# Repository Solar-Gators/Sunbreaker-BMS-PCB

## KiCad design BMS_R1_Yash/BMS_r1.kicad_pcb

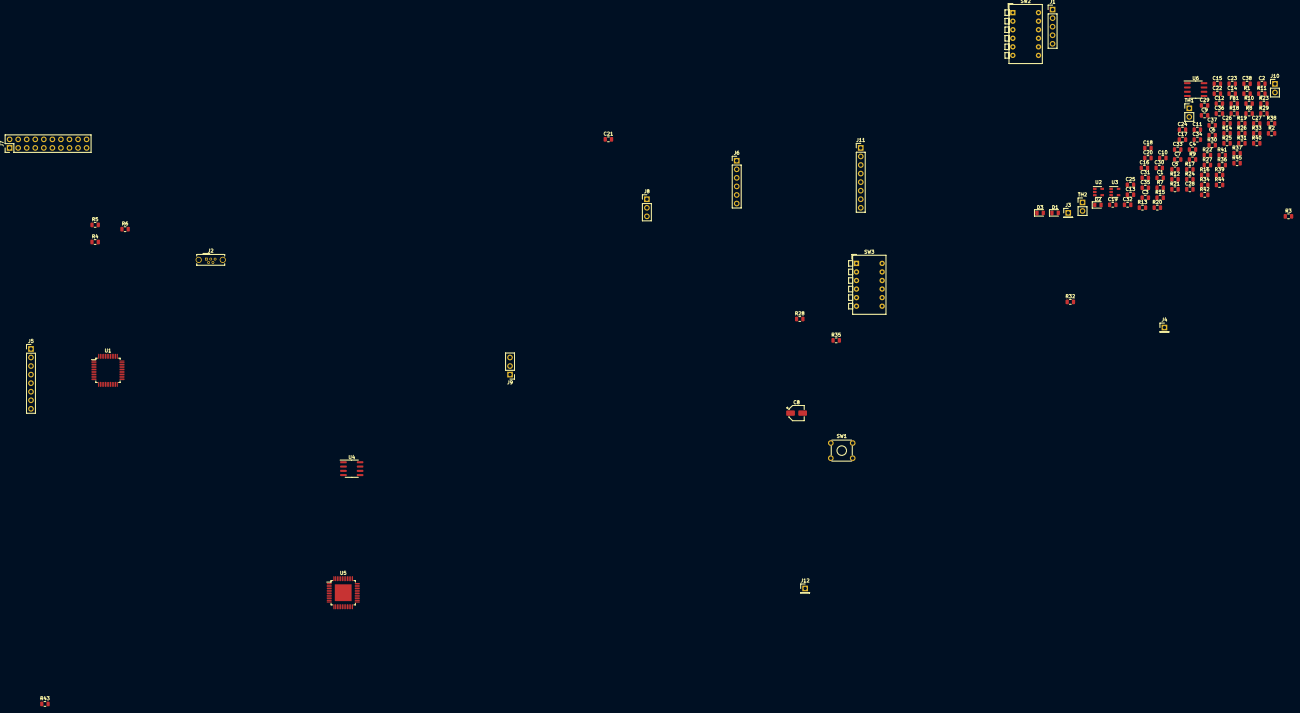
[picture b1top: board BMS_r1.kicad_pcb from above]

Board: 2 copper layers, 110 parts (0 on the bottom side), 95 nets, no tracks yet.

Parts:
C1, C2, C3, C5, C7, C9, C10: 0.1u; C_0805_2012Metric
C4, C6, C19, C20, C24, C31, C32: 1u; C_0805_2012Metric
C8: 3.3u; CP_Elec_4x5.7
C11, C14, C25, C26, C36, C37, C38: 2.2u; C_0805_2012Metric
C12, C13, C15, C16, C27, C28: 0.33u; C_0805_2012Metric
C17, C18, C21, C22, C23, C29, C30, C33, C34, C35: 0.47u; C_0805_2012Metric
D1, D2, D3: LED; LED_0805_2012Metric
FB1: Ferrite_Bead; R_0805_2012Metric
J1: PortB; PinHeader_1x05_P2.54mm_Vertical
J2: USB_B_Micro; USB_Micro-B_Wuerth_614105150721_Vertical_CircularHoles
J3: 5V; PinHeader_1x01_P2.54mm_Vertical
J4: GND; PinHeader_1x01_P2.54mm_Vertical
J5: PortA; PinHeader_1x08_P2.54mm_Vertical
J6: BMS_GPIO; PinHeader_1x06_P2.54mm_Vertical
J7: JTAG; PinHeader_2x10_P2.54mm_Vertical
J8: PWR_SEL; PinHeader_1x03_P2.54mm_Vertical
J9: CVDD_SEL; PinHeader_1x03_P2.54mm_Vertical
J10: VPROG; PinHeader_1x02_P2.54mm_Vertical
J11: COM; PinHeader_1x08_P2.54mm_Vertical
J12: I_IN; PinHeader_1x01_P2.54mm_Vertical
R1, R4, R5, R6, R7, R8, R9, R10, R11, R12, R37, R39, R41, R43, R44: 10K; R_0805_2012Metric
R2, R3, R25: 330; R_0805_2012Metric
R13, R14: 120; R_0805_2012Metric
R15, R17, R18, R19, R20, R21, R22, R23: 47; R_0805_2012Metric
R16: 100; R_0805_2012Metric
R24, R26, R27, R28, R35: 100K; R_0805_2012Metric
R29, R30, R31, R32, R33, R34, R36: 10; R_0805_2012Metric
R38, R40, R42: 1K; R_0805_2012Metric
R45: 6.5K; R_0805_2012Metric
SW1: SW_Push; SW_TH_Tactile_Omron_B3F-10xx
SW2: VC_DIP; SW_DIP_SPSTx06_Piano_CTS_Series194-6MSTN_W7.62mm_P2.54mm
SW3: CB_DIP; SW_DIP_SPSTx06_Piano_CTS_Series194-6MSTN_W7.62mm_P2.54mm
TH1, TH2: 10K; PinHeader_1x02_P2.54mm_Vertical
U1: STM32F103C8Tx; LQFP-48_7x7mm_P0.5mm
U2: LP5907MFX-3.3; SOT-23-5
U3: MIC803; SOT-23-5
U4: TCAN1051; SOIC-8_3.9x4.9mm_P1.27mm
U5: BQ79606A-Q1; TQFP-48-1EP_7x7mm_P0.5mm_EP5x5mm
U6: TLV2372; SOIC-8_3.9x4.9mm_P1.27mm

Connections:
+5V: C4.1, C10.1, J2.1, J3.1, J8.1, U2.1, U2.3, U4.3
/AVDD: C25.1, U5.44
/BMS_GPIO1: J6.1, R37.1, TH1.2, U5.27
/BMS_GPIO2: J6.2, R38.2, U5.28
/BMS_GPIO3: J6.3, U5.29
/BMS_GPIO4: J6.4, U5.30
/BMS_GPIO5: J6.5, U1.27, U5.31
/BMS_GPIO6: D3.2, J6.6, U5.32
/BMS_NFAULT: R35.2, U1.26, U5.42
/BMS_RX: R26.2, U1.21, U5.41
/BMS_TX: R24.2, U1.22, U5.40
/BMS_WAKEUP: R28.2, U1.25, U5.16
/CANH: R13.1, R14.1, U4.7
/CANL: R13.2, R14.2, U4.6
/CAN_RX: U1.32, U4.4
/CAN_S: U1.30, U4.8
/CAN_TX: U1.33, U4.1
/CB0: C34.2, C35.1, R36.1, SW3.7, U5.13
/CB1: C28.2, C33.2, C34.1, R34.1, SW3.6, SW3.8, U5.11
/CB2: SW3.5, SW3.9, U5.9
/CB3: C31.2, C32.1, R32.1, SW3.4, SW3.10, U5.7
/CB4: C27.2, C30.2, C31.1, R31.1, SW3.3, SW3.11, U5.5
/CB5: C27.1, C29.2, C30.1, R30.1, SW3.2, SW3.12, U5.3
/CB6: C29.1, R29.1, SW3.1, U5.1
/CELL0: R23.2, R36.2
/CELL1: R22.2, R34.2
/CELL2: R21.2, R33.2
/CELL3: R20.2, R32.2
/CELL4: R19.2, R31.2
/CELL5: R18.2, R30.2
/CELL6: J8.3, R17.2, R29.2
/COMHN: J11.2, U5.21
/COMHP: J11.1, U5.22
/COMLN: J11.6, U5.20
/COMLP: J11.5, U5.19
/CVDD: C26.1, J9.2, U5.25
/DVDD: C36.1, U5.36
/FAULTHN: J11.4, U5.23
/FAULTHP: J11.3, U5.24
/FAULTLN: J11.8, U5.18
/FAULTLP: J11.7, U5.17
/I_AMP: R45.1, U6.7
/I_IN: J12.1, R40.2
/REFH: C14.1, U5.46
/RST: J7.15, R12.2, SW1.2, U1.7, U3.2
/TCK: J7.9, R7.1, U1.37
/TDI: J7.5, R5.1, U1.38
/TDO: J7.13, R8.1, U1.39
/TMS: J7.7, R6.1, U1.34
/TRST: J7.3, R4.1, U1.40
/TSREF: C11.1, R39.1, TH1.1, U5.43
/VC0: C22.2, C23.1, R23.1, SW2.7, U5.14
/VC1: C16.2, C21.2, C22.1, R22.1, SW2.6, SW2.8, U5.12
/VC2: C16.1, C20.2, C21.1, R21.1, SW2.5, SW2.9, U5.10
/VC3: SW2.4, SW2.10, U5.8
/VC4: C15.2, C18.2, C19.1, R19.1, SW2.3, SW2.11, U5.6
/VC5: C15.1, C17.2, C18.1, R18.1, SW2.2, SW2.12, U5.4
/VC6: C17.1, R17.1, SW2.1, U5.2
/VLDO: C37.1, J9.3, U5.39
GND: C1.2, C2.2, C3.2, C4.2, C5.2, C6.2, C7.2, C8.2, C9.2, C10.2, C11.2, C12.2, C13.2, C14.2, C23.2, C24.2, C25.2, C26.2, C35.2, C36.2, C37.2, C38.2, J2.5, J4.1, J7.4, J7.6, J7.8, J7.10, J7.12, J7.14, J7.16, J7.18, J7.20, J10.2, R1.2, R2.2, R3.2, R9.2, R10.2, R11.2, R25.2, R27.2, R37.2, R41.1, R44.1, SW1.1, TH2.2, U1.8, U1.23, U1.35, U1.47, U2.2, U3.1, U4.2, U5.15, U5.26, U5.35, U5.45, U5.49, U6.4
unnamed: C12.1, R16.1, U5.48
unnamed: C13.1, R15.1, U5.37
unnamed: C19.2, C20.1, R20.1
unnamed: C24.1, J10.1, R27.1, U5.34
unnamed: C28.1, C32.2, C33.1, R33.1
unnamed: D1.1, R2.1
unnamed: D1.2, U1.31
unnamed: D2.1, R3.1
unnamed: D3.1, R25.1
unnamed: J1.1, U1.41
unnamed: J1.2, U1.42
unnamed: J1.3, U1.43
unnamed: J1.4, U1.45
unnamed: J1.5, U1.46
unnamed: J5.1, U1.10
unnamed: J5.2, U1.11
unnamed: J5.3, U1.12
unnamed: J5.4, U1.13
unnamed: J5.5, U1.14
unnamed: J5.6, U1.15
unnamed: J5.7, U1.16
unnamed: J5.8, U1.17
unnamed: J7.11, R10.1
unnamed: J7.17, R11.1
unnamed: J7.19, R9.1
unnamed: J8.2, J9.1, R15.2, R16.2
unnamed: R1.1, U1.44
unnamed: R38.1, R39.2, TH2.1
unnamed: R40.1, R42.2, U6.2
unnamed: R41.2, U6.3
unnamed: R42.1, R43.2, U6.1
unnamed: R43.1, R45.2, U6.6
unnamed: R44.2, U6.5
VDD: C1.1, C2.1, C3.1, C6.1, C7.1, C9.1, C38.1, D2.2, FB1.2, J7.1, J7.2, R4.2, R5.2, R6.2, R7.2, R8.2, R12.1, R24.1, R26.1, R28.1, R35.1, U1.24, U1.36, U1.48, U2.5, U3.3, U4.5, U5.33, U6.8
VDDA: C5.1, C8.1, FB1.1, U1.9

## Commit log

2020-08-03 All the BMS Files for Revision 1
    I have all the KiCad files included here for BMS R1, but this one doesn't have the routing done. I think Nate has a copy with that?
